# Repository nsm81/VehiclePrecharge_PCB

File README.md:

# VehiclePrecharge_PCB
The precharge board contains the precharge resistors, precharge relay, main relay drivers (with economisers), and a controlling micro.

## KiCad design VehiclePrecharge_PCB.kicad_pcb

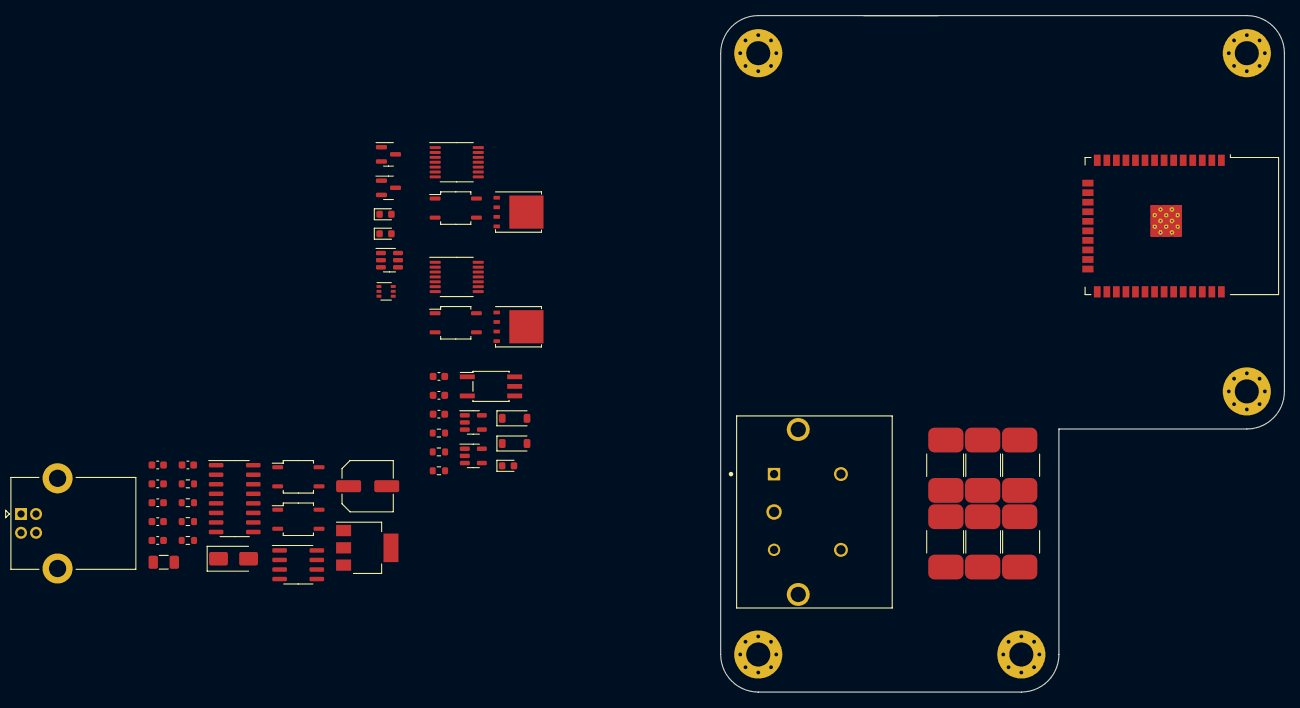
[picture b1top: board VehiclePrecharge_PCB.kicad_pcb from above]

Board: 4 copper layers, 75.0 x 90.0 mm, 56 parts (0 on the bottom side), 43 nets.

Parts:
C1, C2, C3, C6, C7, C8, C9: 100n; C_0603_1608Metric
C4: 22u; C_Elec_6.3x7.7
C5: 0.1uF; C_0603_1608Metric
C10: 1u; C_0603_1608Metric
D1: SS34; D_SMA
D2, D5: GREEN; LED_0603_1608Metric
D3: SM712_SOT23; SOT-23
D4, D6: 1N4148W; D_SOD-123
D7: Green; LED_0603_1608Metric
F1: 2A; Fuse_1206_3216Metric
H1, H2, H2#2, H3, H4: M3; MountingHole_3.2mm_M3_Pad_Via
J1: USB_B; USB_B_Lumberg_2411_02_Horizontal
K1: 2-1904058-5; Precharge Relay
Q1: BC847BS; SOT-363_SC-70-6
Q2: SSM3J328R LF; SOT-23
Q3, Q4: FDMS86255; TDSON-8-1
R6, R8, R11: 10k; R_0603_1608Metric
R9: 2.2k; 2817 Package
R10, R12: 10k; 2817 Package
R13: 120; R_0603_1608Metric
R14: 2.2k; R_0603_1608Metric
R16, R19: 1k; R_0603_1608Metric
R17, R18, R22: R_Small; 2817 Package
U1, U10: MCP9502PT-115E; SOT-23-5
U4, U12, U13, U14: AQY212; SOP-4_3.8x4.1mm_P2.54mm
U5: CH340C; SOIC-16_3.9x9.9mm_P1.27mm
U6: ESP32-WROOM-32
U7: USBLC6-2SC6; SOT-23-6
U8: AMS1117-3.3; SOT-223-3_TabPin2
U9: SN65HVD230; SOIC-8_3.9x4.9mm_P1.27mm
U11: TLP2361; SO-5_4.4x3.6mm_P1.27mm
U15, U16: DRV110A; TSSOP-14_4.4x5mm_P0.65mm

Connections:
+3V3: C2.2, C3.2, C5.2, C10.1, D5.2 (A), R8.2, U5.4 (V3), U5.16 (VCC), U6.2 (VDD), U8.2 (VO), U9.3 (VCC)
+5V: C8.1, D1.1 (K), D7.2 (A), F1.1, U4.3, U7.5 (VBUS), U11.6 (VDD)
+5VA: C6.2, C7.2, U1.3 (Hyst), U1.4 (VDD), U10.3 (Hyst), U10.4 (VDD)
CAN+: D3.2 (A2), R13.2, U9.7 (CANH)
CAN-: D3.1 (A1), R13.1, U9.6 (CANL)
CAN_RX: U6.11 (IO26), U9.4 (R)
CAN_TX: U6.13 (IO14), U9.1 (D)
D+: J1.3 (D+), U7.1 (I/O1)
D+ Out: U5.5 (UD+), U7.6 (I/O1)
D-: J1.2 (D-), U7.3 (I/O2)
D- Out: U5.6 (UD-), U7.4 (I/O2)
DTR: Q1.4 (E2), R10.2, U5.13 (~DTR)
EN: C1.1, Q1.6 (C1), R8.1, U6.3 (EN)
GND: C1.2, C2.1, C3.1, C4.2, C5.1, C8.2, C9.2, C10.2, D3.3 (common), J1.4 (GND), K1.2, Q2.1 (G), R9.1, R12.2, R14.1, R17.2, R22.2, U5.1 (GND), U6.1 (GND), U6.15 (GND), U6.38 (GND), U6.39 (GND), U7.2 (GND), U8.1 (GND), U9.2 (GND), U11.4 (GND), U15.5 (OSC), U15.8 (GND), U16.5 (OSC), U16.8 (GND)
HV-: C6.1, C7.1, R6.1, R16.1, U1.1 (GND), U1.2 (GND), U10.1 (GND), U10.2 (GND)
IO0: Q1.3 (C2), U6.25 (IO0)
unnamed: D1.2 (A), J1.1 (VBUS)
unnamed: D2.1 (K), R9.2
unnamed: D4.2 (A), U1.5 (Out)
unnamed: D4.1 (K), D6.1 (K), R6.2, U11.1 (A)
unnamed: D5.1 (K), R14.2
unnamed: D6.2 (A), U10.5 (Out)
unnamed: D7.1 (K), R19.2
unnamed: R18.2, U13.3
unnamed: K1.1, U12.3
unnamed: Q1.2 (B1), R10.1
unnamed: Q1.5 (B2), R11.1
unnamed: F1.2, Q2.3 (D)
unnamed: C4.1, C9.1, Q2.2 (S), U8.3 (VI)
unnamed: Q3.4 (G), U15.11 (OUT)
unnamed: Q4.4 (G), U16.11 (OUT)
unnamed: R17.1, U12.2
unnamed: R12.1, U9.8 (Rs)
unnamed: R16.2, U11.3 (K)
unnamed: Q3.1 (S), Q3.2 (S), Q3.3 (S), U15.9 (SENSE)
unnamed: R18.1, U15.7 (VIN)
unnamed: R22.1, U16.4 (HOLD)
unnamed: Q4.1 (S), Q4.2 (S), Q4.3 (S), U16.9 (SENSE)
POC_FLT: R19.1, U11.5 (VO)
RTS: Q1.1 (E1), R11.2, U5.14 (~RTS)
RxD: U5.3 (RXD), U6.35 (TXD0/IO1)
Shutdown Loop: U4.1, U12.4, U13.4, U14.4
TxD: U5.2 (TXD), U6.34 (RXD0/IO3)

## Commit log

2023-06-27 Schematic Initial Commit
2023-06-29 More schematic completed
2023-07-03 Changed to DRV110A
